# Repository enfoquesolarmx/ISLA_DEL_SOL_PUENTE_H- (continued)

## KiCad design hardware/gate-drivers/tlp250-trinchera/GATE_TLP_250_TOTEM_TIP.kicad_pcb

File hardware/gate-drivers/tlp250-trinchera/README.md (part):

# Módulo gate driver de medio puente H con TLP250H — modo trinchera (legacy) con tótem TIP41C/TIP42C

**Proyecto:** Puente H — prototipo SPWM "Isla del Sol" (inversor 48 V → 127 V / 60 Hz, 1000 W; modo cargador 1 kVA)
**Módulo:** gate driver de **medio puente H** (una rama: MOSFET alto + MOSFET bajo), de servicio / legacy, intercambiable con IRS2186 y UCC21520DW (misma interfaz, mismo firmware)
**Versión de placa:** V.0.1.NOV.26.J.G
**Estado:** diseño terminado (esquemático y layout); esquemático por bloques con guía de trinchera (2026-11-12). Pendiente: DRC final, fabricación y validación en banco
**Fecha:** 2026-11-02 · **Revisión:** 2026-11-03 (diseño final) · 2026-11-12 (esquemático por bloques)
**Documentos relacionados:** `identificacion_dt_pin9.md` (P9, llave en posición 8, poka-yoke), `compensacion_adaptativa_tiempo_muerto.md`

| Cara de componentes | Cara de soldadura |
| --- | --- |
|  |  |

*Izquierda: arriba, la bornera J1 de entrada, con R3/R4 (330 Ω) en serie con los LED y R1/R2 (10 kΩ) a GND; en medio, los **dos TLP250H** (DIP-8), uno por canal; abajo, los dos tótems **acostados**, TIP41C (NPN) y TIP42C (PNP) con sus resistencias de 2.2 Ω, la red de bootstrap (2.2 Ω 1 W + diodo rápido), los 2 × 10 µF del bootstrap y el header J5. Derecha: las leyendas **"TRENZAR H Y L CON GND"**, **"OPERACIÓN DT TLP250 = 1 µs"** y **"OJO: USAR SILICÓN RTV NEUTRO ENTRE TIPs"**, los 0.1 µF pegados a cada TLP, el 10 µF de 15 V, el zener Z1 de 18 V (1SMA5931B) y la **X** de la llave en la posición 8 de J5.*

*Esquemático por bloques (KiCad 9, hoja A3), pensado para quien arma y repara: **A** entrada J1 · **B** optoacoplador del canal alto (U1) · **C** optoacoplador del canal bajo (U2) · **D** 15 V del canal bajo · **E** bootstrap · **F** tótem alto · **G** tótem bajo · **H** salida J5 · **I** guía rápida de trinchera. Cada bloque dice qué medir y qué pasa si una pieza va al revés.*

## 0. Guía rápida de trinchera

**TLP250 o TLP250H: no son iguales.**

| | TLP250H (diseño) | TLP250 "viejo" (sin H, rescatado) |
| --- | --- | --- |
| Corriente de alimentación | **3 mA máx.** | **11 mA máx.** (7 mA típ.) |
| UVLO | Sí, 7.5–9.5 V | **No especificado** |
| Rama A (24 kHz, el bootstrap se recarga cada 42 µs) | ✓ | ✓ |
| Rama B (60 Hz, 8.3 ms sin recargar) | ✓ VB1 ≈ 11.8 V | ✗ VB1 cae ~5–8 V → el MOSFET alto queda a medio encender y sin protección |

**Regla:** un TLP250 sin "H" solo va en el módulo de la **rama A** (o en las dos en modo cargador, a 24 kHz). En la rama B del inversor, TLP250H u otro módulo (IRS2186, IR2110, UCC21520).

**Antes de soldar:**

| Pieza | Cuidado | Si se hace mal |
| --- | --- | --- |
| U1, U2 | Zócalo DIP-8, muesca hacia el pin 1; revisar la letra **H** | Al revés no enciende; sin H, ver la tabla anterior |
| R3, R4 | **330 Ω** con MCU de 5 V | Con 1 kΩ el LED no enciende bien (~1.7 mA) |
| J5 | **Quitar el pin 8** del header (llave) | El módulo podría entrar al revés |
| Z1 | Banda (cátodo) hacia **VB1** | Pone en corto el bootstrap: el MOSFET alto nunca enciende |
| Q1–Q4 | NPN (TIP41C / D44H11G) en Q1 y Q4, PNP (TIP42C / D45H11G) en Q2 y Q3; acostados, aletas sin tocarse | Cruzados: la salida no sigue a la entrada; aletas juntas: corto VB1–GND_K |
| TIPs | Silicón RTV **neutro** | El acético corroe; el caliente se ablanda a 60–80 °C |

**Prueba sin MOSFET** (15 V en J5-7; J5-4 a la tierra de la fuente; **J5-2 (VS1) unido a J5-4** para que cargue el bootstrap; J1 a la tarjeta de control o a 5 V):

| Medir | Entre | Debe dar |
| --- | --- | --- |
| Salidas con J1 suelto | HA_OUT (J5-1) y LA_OUT (J5-5) | 0 V |
| L = 5 V | LA_OUT a GND_K | ≈ 14 V |
| H = 5 V (después de un pulso de L) | HA_OUT a VS1 | ≈ 13 V |
| Corriente del LED | Caída en R3 o R4 | ≈ 3.3 V (~10 mA) |
| Aislamiento | J1-GND contra GND_K y contra VS1 | **Sin continuidad** |
| Tiempo muerto | Lo que reporta el MCU | **1 µs** (P9 abierto) |

---

## 1. Propósito

### 1.1 Qué maneja este módulo

Cada módulo es un **gate driver de medio puente**: maneja **una rama** del puente H, es decir, el **MOSFET del lado alto** (canal H, referido a VS1, alimentado por bootstrap) y el **MOSFET del lado bajo** (canal L, referido a GND_K) de esa rama.

```
            +48 V
              │
     HA ──► [MOSFET alto]          [MOSFET alto] ◄── HB
              │                         │
              ├── VS1 ──► transformador ◄── VS2 ──┤
              │                         │
     LA ──► [MOSFET bajo]          [MOSFET bajo] ◄── LB
              │                         │
             GND ───────────────────── GND
         └── módulo rama A ──┘    └── módulo rama B ──┘
```

- **El puente H completo usa dos módulos:** uno en la **rama A** (VS1) y otro en la **rama B** (VS2). Son el mismo módulo; en la rama B, las señales "H" y "L" de J1 manejan HB y LB, y el pin "VS1" de J5 se conecta a VS2.
- **Inversor (modulación híbrida):** el módulo de la rama A conmuta a **24 kHz** y el de la rama B a **60 Hz**.
- **Cargador (unipolar):** los dos módulos conmutan a **24 kHz**.
- Cada posición (alto o bajo) puede tener **1 o 2 MOSFET en paralelo** (sección 5).
- Se pueden mezclar tecnologías entre ramas (por ejemplo, UCC21520 en la rama A y TLP250 en la rama B): el MCU lee P9 de cada módulo y, si cualquiera pide 1 µs, usa 1 µs en todo el puente.

### 1.2 Por qué existe

Este módulo existe para **cuando TI o Infineon no llegan**. Es una opción **educativa y de supervivencia**: demuestra que el puente H puede operar con componentes legacy que se consiguen en cualquier tienda de electrónica o se rescatan de equipos viejos (variadores, UPS, soldadoras inverter, fuentes, amplificadores).

| Criterio | Módulos IRS2186 / UCC21520 | Módulo TLP250 (este) |
| --- | --- | --- |
| Costo y número de componentes | **Menor** ✓ | Mayor |
| Desempeño (DT, THD) | **500 ns, THD ~0.8 %** ✓ | 1 µs, THD ~1.6 % |
| Disponibilidad en zonas aisladas | Baja (distribuidor, importación) | **Alta: tienda local o rescate** ✓ |
| Reparación a mano | SMD fino | **DIP y TO-220, cautín común** ✓ |
| Aislamiento entrada / potencia | IRS: no aislado · UCC: aislado | **Aislado (optoacoplador)** ✓ |
| Valor educativo | Driver integrado ("caja negra") | **Cada etapa visible y medible** ✓ |

**Conclusión de diseño:** para producción se usan IRS2186 o UCC21520. Este módulo no busca eficientar; busca que **siempre exista una alternativa**. La infraestructura que lo soporta (P9 y llave en posición 8) cuesta ~1 USD y queda en todas las tarjetas.

---

## 2. Interfaz

### 2.1 J1 — entrada, hacia la tarjeta de control (bornera de 5 terminales)

| Terminal | Señal | En este módulo |
| --- | --- | --- |
| 1 | H | Ánodo del LED de U1 (vía R3) |
| 2 | GND | Cátodo del LED de U1 (trenzar con H) |
| 3 | L | Ánodo del LED de U2 (vía R4) |
| 4 | GND | Cátodo del LED de U2 (trenzar con L) |
| **5** | **P9 — ID DT** | **Abierto, sin pista** → el MCU usa **1 µs** |

- Serigrafía: **"TRENZAR H Y L CON GND"** y **"OPERACION DT TLP250=1US"**.
- **P9 tiene como vecino un GND (terminal 4).** Cable con **puntas estañadas o terminal**, sin hilos sueltos. Opcional: no instalar el cable P9 (la pull-up de la tarjeta de control lee 1 → 1 µs).
- El GND de J1 es el GND del MCU y **no se une a GND_K ni a la potencia dentro del módulo**: el optoacoplador aísla la entrada.

### 2.2 J5 — salida, hacia la tarjeta del puente H (header de 9 posiciones, 2.54 mm)

| Pin | Señal | En este módulo |
| --- | --- | --- |
| 1 | HA_OUT | Emisores del tótem H |
| 2 | VS1 | Referencia del canal H |
| 3 | — | Libre (separación del nodo conmutado) |
| 4 | GND_K | Referencia Kelvin del canal L |
| 5 | LA_OUT | Emisores del tótem L |
| 6 | — | **Sin conectar** en este módulo (la entrada está aislada); marcado como no conectado en el esquemático |
| 7 | 15 V | Alimentación |
| 8 | — | **Llave mecánica:** sin pad; **quitar el pin 8 del header**; "X" en serigrafía |
| 9 | — | Reservado, abierto |

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
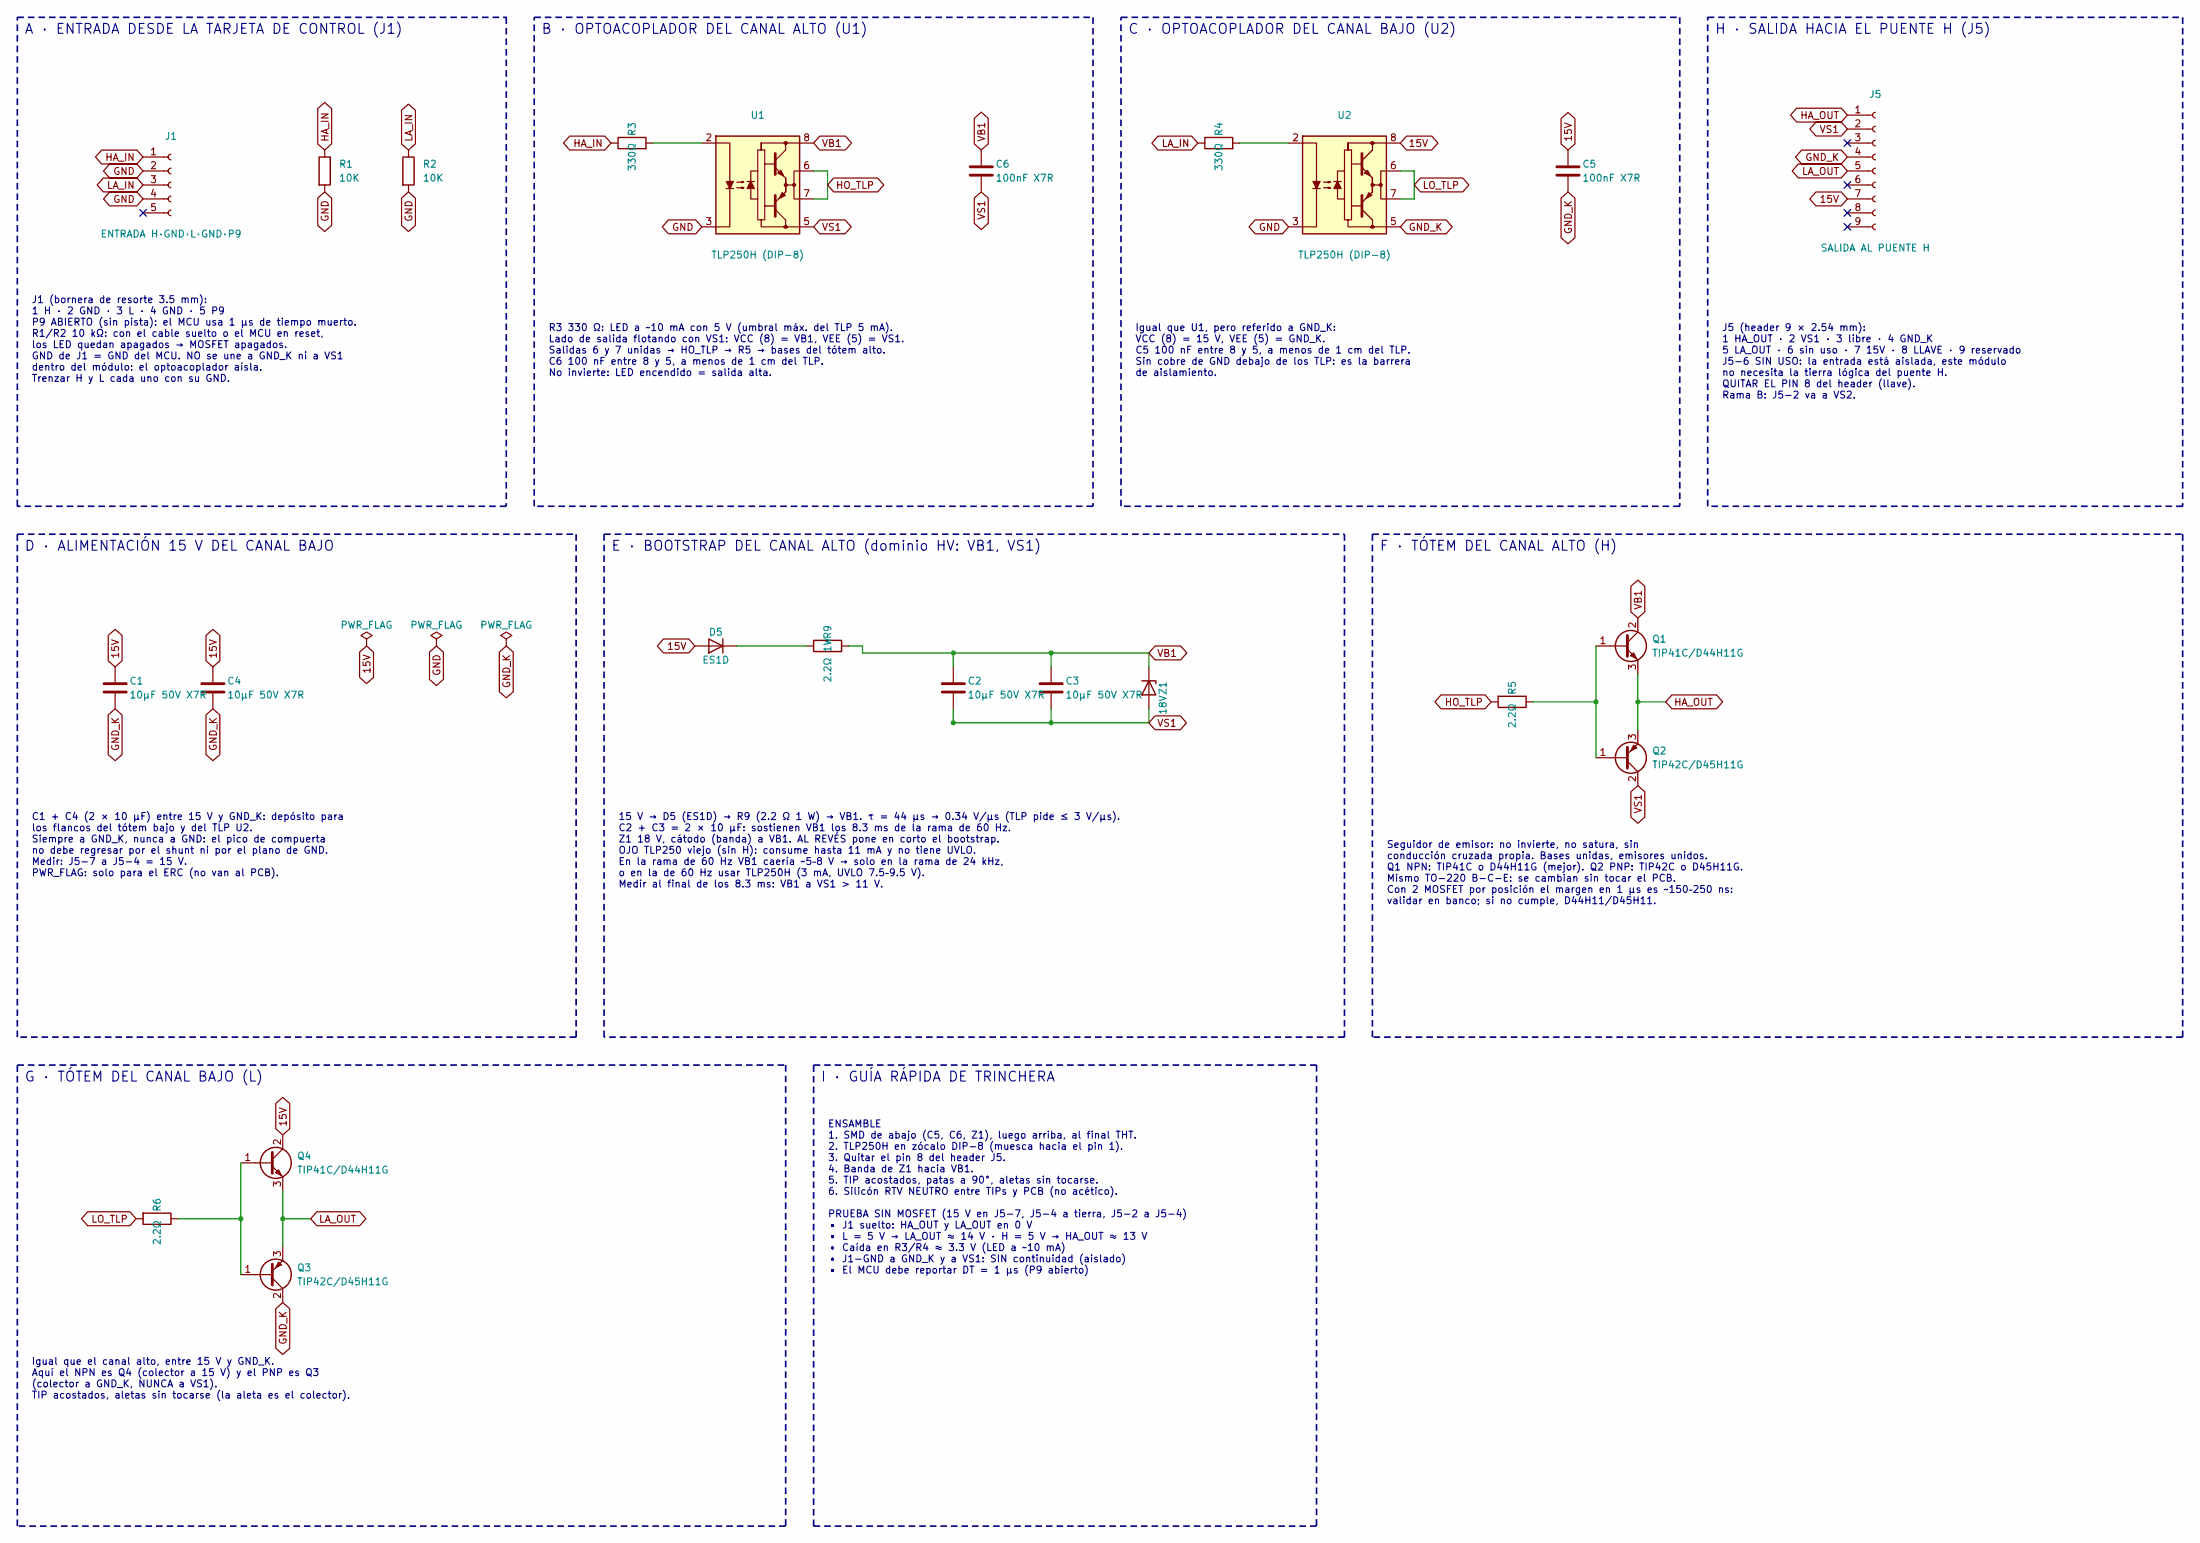
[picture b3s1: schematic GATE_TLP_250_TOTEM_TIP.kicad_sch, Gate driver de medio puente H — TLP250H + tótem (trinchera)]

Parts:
C1, C2, C3, C4: 10µF 50V X7R; C_1206_3216Metric
C5, C6: 100nF X7R; C_1206_3216Metric
D5: ES1D; D_SMA
J1: ENTRADA H·GND·L·GND·P9; PhoenixContact_SPT_1.5_5-H-3.5_1x05_P3.5mm_Horizontal
J5: SALIDA AL PUENTE H; PinHeader_1x09_P2.54mm_Vertical
Q1, Q4: TIP41C/D44H11G; TO-220-3_Vertical
Q2, Q3: TIP42C/D45H11G; TO-220-3_Vertical
R1, R2: 10K; R_1206_3216Metric_Pad1.30x1.75mm_HandSolder
R3, R4: 330Ω; R_1206_3216Metric_Pad1.30x1.75mm_HandSolder
R5, R6: 2.2Ω; R_1206_3216Metric_Pad1.30x1.75mm_HandSolder
R9: 2.2Ω 1W; R_1210_3225Metric
U1, U2: TLP250H (DIP-8); DIP-8_W7.62mm
Z1: 18V; D_SMA

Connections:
15V: C1.1, C4.1, C5.1, D5.2 (A), J5.7, Q4.2 (C), U2.8 (VCC)
GND: J1.2, J1.4, R1.2, R2.2, U1.3 (C), U2.3 (C)
GND_K: C1.2, C4.2, C5.2, J5.4, Q3.2 (C), U2.5 (VEE)
HA_IN: J1.1, R1.1, R3.1
HA_OUT: J5.1, Q1.3 (E), Q2.3 (E)
HO_TLP: R5.2, U1.6 (VO), U1.7 (VO)
LA_IN: J1.3, R2.1, R4.1
LA_OUT: J5.5, Q3.3 (E), Q4.3 (E)
LO_TLP: R6.2, U2.6 (VO), U2.7 (VO)
unnamed: D5.1 (K), R9.2
unnamed: Q1.1 (B), Q2.1 (B), R5.1
unnamed: Q3.1 (B), Q4.1 (B), R6.1
unnamed: R3.2, U1.2 (A)
unnamed: R4.2, U2.2 (A)
VB1: C2.1, C3.1, C6.1, Q1.2 (C), R9.1, U1.8 (VCC), Z1.1 (K)
VS1: C2.2, C3.2, C6.2, J5.2, Q2.2 (C), U1.5 (VEE), Z1.2 (A)

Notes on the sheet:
A · ENTRADA DESDE LA TARJETA DE CONTROL (J1)
J1 (bornera de resorte 3.5 mm): 1 H · 2 GND · 3 L · 4 GND · 5 P9 P9 ABIERTO (sin pista): el MCU usa 1 µs de tiempo muerto. R1/R2 10 kΩ: con el cable suelto o el MCU en reset, los LED quedan apagados → MOSFET apagados. GND de J1 = GND del MCU. NO se une a GND_K ni a VS1 dentro del módulo: el optoaco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
B · OPTOACOPLADOR DEL CANAL ALTO (U1)
R3 330 Ω: LED a ~10 mA con 5 V (umbral máx. del TLP 5 mA). Lado de salida flotando con VS1: VCC (8) = VB1, VEE (5) = VS1. Salidas 6 y 7 unidas → HO_TLP → R5 → bases del tótem alto. C6 100 nF entre 8 y 5, a menos de 1 cm del TLP. No invierte: LED encendido = salida alta.
C · OPTOACOPLADOR DEL CANAL BAJO (U2)
Igual que U1, pero referido a GND_K: VCC (8) = 15 V, VEE (5) = GND_K. C5 100 nF entre 8 y 5, a menos de 1 cm del TLP. Sin cobre de GND debajo de los TLP: es la barrera de aislamiento.
H · SALIDA HACIA EL PUENTE H (J5)
J5 (header 9 × 2.54 mm): 1 HA_OUT · 2 VS1 · 3 libre · 4 GND_K 5 LA_OUT · 6 sin uso · 7 15V · 8 LLAVE · 9 reservado J5-6 SIN USO: la entrada está aislada, este módulo no necesita la tierra lógica del puente H. QUITAR EL PIN 8 del header (llave). Rama B: J5-2 va a VS2.
D · ALIMENTACIÓN 15 V DEL CANAL BAJO
C1 + C4 (2 × 10 µF) entre 15 V y GND_K: depósito para los flancos del tótem bajo y del TLP U2. Siempre a GND_K, nunca a GND: el pico de compuerta no debe regresar por el shunt ni por el plano de GND. Medir: J5-7 a J5-4 = 15 V. PWR_FLAG: solo para el ERC (no van al PCB).
E · BOOTSTRAP DEL CANAL ALTO (dominio HV: VB1, VS1)
15 V → D5 (ES1D) → R9 (2.2 Ω 1 W) → VB1. τ = 44 µs → 0.34 V/µs (TLP pide ≤ 3 V/µs). C2 + C3 = 2 × 10 µF: sostienen VB1 los 8.3 ms de la rama de 60 Hz. Z1 18 V, cátodo (banda) a VB1. AL REVÉS pone en corto el bootstrap. OJO TLP250 viejo (sin H): consume hasta 11 mA y no tiene UVLO. En la rama de 60 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
F · TÓTEM DEL CANAL ALTO (H)
Seguidor de emisor: no invierte, no satura, sin conducción cruzada propia. Bases unidas, emisores unidos. Q1 NPN: TIP41C o D44H11G (mejor). Q2 PNP: TIP42C o D45H11G. Mismo TO-220 B-C-E: se cambian sin tocar el PCB. Con 2 MOSFET por posición el margen en 1 µs es ~150–250 ns: validar en banco; si no 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
G · TÓTEM DEL CANAL BAJO (L)
Igual que el canal alto, entre 15 V y GND_K. Aquí el NPN es Q4 (colector a 15 V) y el PNP es Q3 (colector a GND_K, NUNCA a VS1). TIP acostados, aletas sin tocarse (la aleta es el colector).
I · GUÍA RÁPIDA DE TRINCHERA
ENSAMBLE 1. SMD de abajo (C5, C6, Z1), luego arriba, al final THT. 2. TLP250H en zócalo DIP-8 (muesca hacia el pin 1). 3. Quitar el pin 8 del header J5. 4. Banda de Z1 hacia VB1. 5. TIP acostados, patas a 90°, aletas sin tocarse. 6. Silicón RTV NEUTRO entre TIPs y PCB (no acético). PRUEBA SIN MOSFE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

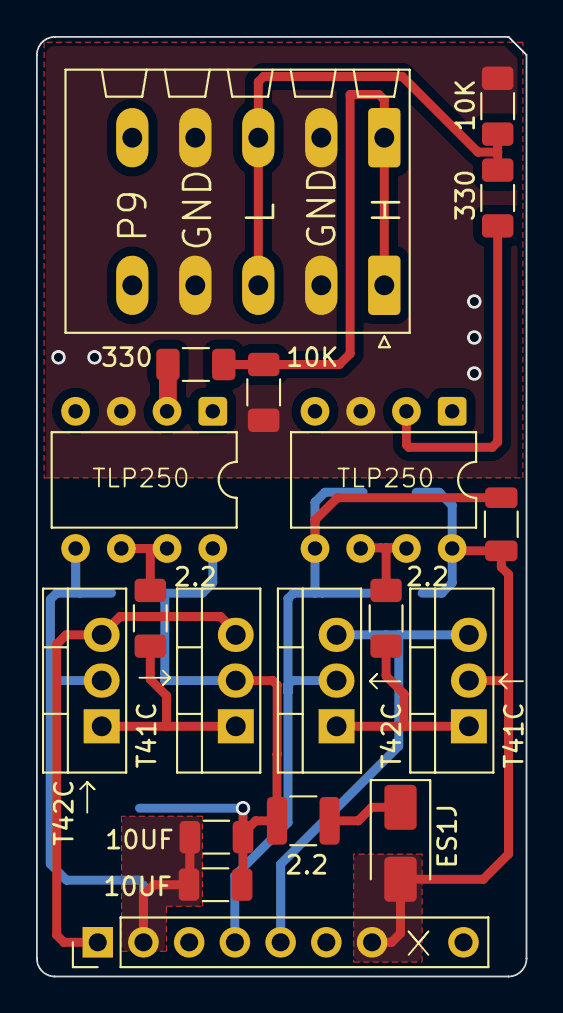
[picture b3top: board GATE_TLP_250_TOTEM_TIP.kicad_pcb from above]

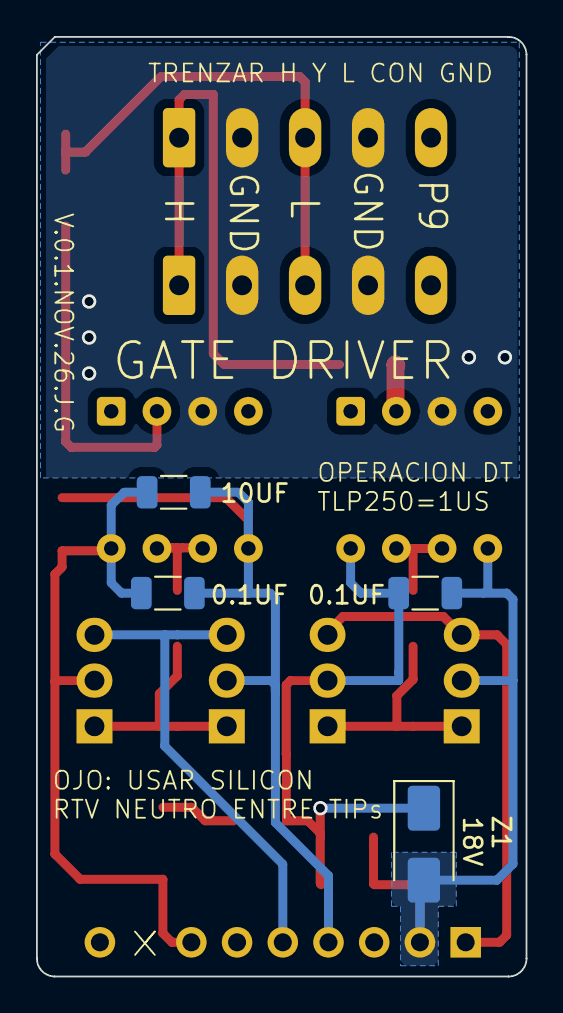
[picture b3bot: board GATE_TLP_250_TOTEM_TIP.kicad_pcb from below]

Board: 2 copper layers, 27.2 x 52.2 mm, 23 parts (4 on the bottom side), 16 nets.

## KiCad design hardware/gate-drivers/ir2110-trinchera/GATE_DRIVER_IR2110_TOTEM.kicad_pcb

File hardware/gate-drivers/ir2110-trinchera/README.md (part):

# Módulo gate driver de medio puente H con IR2110 + tótem TIP41C/TIP42C — modo trinchera

**Proyecto:** Puente H — prototipo SPWM "Isla del Sol" (inversor 48 V → 127 V / 60 Hz, 1000 W; modo cargador 1 kVA)
**Módulo:** gate driver de **medio puente H** (una rama: MOSFET alto + MOSFET bajo), legacy / trinchera, con tótem por canal
**Intercambiable con:** IRS2186, UCC21520DW y TLP250 de trinchera (misma interfaz J2/J5, mismo firmware)
**Versión de placa:** V.0.1.NOV.26.J.G
**Estado:** diseño terminado; DRC con 0 errores y 0 elementos sin conectar; esquemático por bloques con guía de trinchera (2026-11-12). Pendiente: fabricación y validación en banco
**Fecha:** 2026-11-04 (esquemático por bloques: 2026-11-12)
**Documentos relacionados:** [`docs/identificacion_dt_pin9.md`](../../../docs/identificacion_dt_pin9.md), [`docs/sensado_corriente.md`](../../../docs/sensado_corriente.md), [módulo TLP250](../tlp250-trinchera/README.md), [módulo IRS2186](../irs2186/README.md)

| Cara de componentes | Cara de soldadura |
| --- | --- |
|  |  |

*Izquierda: arriba, la bornera J2 de entrada con R1 y R2 (10 kΩ, pull-down de HIN y LIN); en medio, el **IR2110 en DIP-14** con sus capacitores X7R; abajo, los **cuatro TO-220 del tótem** (TIP41C o D44H11 como NPN, TIP42C o D45H11 como PNP) y el header J5 hacia el puente H (H · VS1 · · · GK · L · G · 15V · llave · NC). La leyenda **"USAR SILICÓN RTV NEUTRO ENTRE TIPs"** recuerda fijar los transistores a la tarjeta con silicón de curado neutro. Derecha: la leyenda **"ATENCIÓN: DT = 1 µs — VALIDAR MOSFET Y SW"**, el regulador **78L05** (SOT-89) que da los 5 V de VDD, la red de bootstrap (2.2 Ω 1 W + ES1D), los dos **zener de 18 V** (Z1: VB1–VS1 y Z2: 15V–GND_K) y la **X** de la llave en la posición 8 de J5.*

*Esquemático por bloques (KiCad 9, hoja A3), pensado para quien arma y repara: **A** entrada J2 · **B** lógica de 5 V con 78L05 · **C** IR2110 · **D** 15 V del lado bajo · **E** bootstrap · **F** tótem alto · **G** tótem bajo · **H** salida J5 · **I** guía rápida de trinchera (ensamble y prueba sin MOSFET). Cada bloque dice qué medir y qué pasa si una pieza va al revés.*

## 0. Guía rápida de trinchera

**Antes de soldar:**

| Pieza | Cuidado | Si se hace mal |
| --- | --- | --- |
| U1 IR2110 | En **zócalo DIP-14**, muesca hacia el pin 1 | Se cambia sin cautín; al revés se quema al conectar |
| J5 | **Quitar el pin 8** del header (llave) | El módulo podría entrar al revés en el puente H |
| Z1 | Banda (cátodo) hacia **VB1** | Pone en corto el bootstrap: el MOSFET alto nunca enciende |
| Z2 | Banda (cátodo) hacia **15 V** | Se calienta y jala los 15 V |
| Q1–Q4 | NPN (TIP41C / D44H11G) arriba, PNP (TIP42C / D45H11G) abajo; acostados, aletas sin tocarse | NPN y PNP cruzados: la salida no sigue a la entrada |
| TIPs | Silicón RTV **neutro** entre los cuerpos y el PCB | El silicón acético corroe las patas |

**Prueba sin MOSFET** (15 V en J5-7; J5-6 y J5-4 a la tierra de la fuente; **J5-2 (VS1) unido a J5-4** para que cargue el bootstrap; J2 a la tarjeta de control o a 5 V):

| Medir | Entre | Debe dar |
| --- | --- | --- |
| VDD | Pin 9 y pin 13 del IR2110 | 5.0 V ± 0.25 V |
| VCC | Pin 3 y pin 2 | 15 V |
| SD | Pin 11 a GND | 0 V |
| Salidas con J2 suelto | HA_OUT (J5-1) y LA_OUT (J5-5) | 0 V |
| L = 5 V | LA_OUT a GND_K | ≈ 14 V (15 V menos el V_BE del tótem) |
| H = 5 V (después de un pulso de L, para cargar el bootstrap) | HA_OUT a VS1 | ≈ 13 V |
| Tiempo muerto | Lo que reporta el MCU | **1 µs** (P9 abierto) |

> Valores verificados contra `GATE_DRIVER_IR2110_TOTEM.kicad_pcb` (2026-11-04). Lo marcado *(verificar)* depende de la hoja de datos.

---
## 1. Qué maneja este módulo

Cada módulo maneja **una rama** del puente H: el **MOSFET del lado alto** (HO, referido a VS, alimentado por bootstrap) y el **MOSFET del lado bajo** (LO, referido a COM / GND_K).

```
            +48 V
              │
     HA ──► [MOSFET alto]          [MOSFET alto] ◄── HB
              │                         │
              ├── VS1 ──► transformador ◄── VS2 ──┤
              │                         │
     LA ──► [MOSFET bajo]          [MOSFET bajo] ◄── LB
              │                         │
             GND ───────────────────── GND
         └── módulo rama A ──┘    └── módulo rama B ──┘
```

- **El puente completo usa dos módulos iguales:** rama A (VS1) y rama B (VS2). En la rama B, "H" y "L" de J2 manejan HB y LB, y el pin "VS1" de J5 va a VS2.
- **Inversor (modulación híbrida):** rama A a **24 kHz**, rama B a **60 Hz**. **Cargador (unipolar):** las dos ramas a **24 kHz**.
- **Alcance: de 1 a 5 MOSFET por posición** (sección 6).

### 1.1 Por qué existe: modo trinchera

Igual que el módulo TLP250, este módulo existe para **cuando los drivers modernos no llegan**. El IR2110 (International Rectifier, hoy Infineon) es el driver de medio puente **más fácil de conseguir o rescatar**: está en variadores, soldadoras inverter y UPS viejos, y en casi cualquier tienda de electrónica. Viene en **DIP-14**: se monta en zócalo y se cambia sin cautín. Todo el módulo se arma con partes de tienda local.

| | TLP250 + tótem | **IR2110 + tótem (este)** |
| --- | --- | --- |
| Driver | Optoacoplador DIP-8, uno por canal | DIP-14, un chip para los dos canales |
| Aislamiento de la entrada | Sí (óptico) | Parcial: **VSS y COM separados**, hasta ±5 V |
| Diferencia de retardo entre canales | Hasta **400 ns** | **10–20 ns** |
| Margen dentro de 1 µs | ~150–250 ns con 2 IRF100P219 | **Mucho mayor** |
| Corriente propia | ~2 A | 2 A |
| MOSFET por posición | 1–2 IRF100P219 | **1–5** (por ejemplo 5 × IRF540N) |

---

## 2. Interfaz

### 2.1 J2 — entrada, hacia la tarjeta de control ("J1" de la interfaz)

Conector **Phoenix Contact SPT 1,5/5-H-3,5** (5 posiciones, paso 3.5 mm, de resorte), igual que el módulo IRS2186.

| Terminal | Señal | En este módulo |
| --- | --- | --- |
| 1 | H | HIN del IR2110 (pin 10), 10 kΩ a GND |
| 2 | GND | Tierra lógica = VSS (trenzar con H) |
| 3 | L | LIN del IR2110 (pin 12), 10 kΩ a GND |
| 4 | GND | Tierra lógica = VSS (trenzar con L) |
| **5** | **P9 — ID DT** | **Abierto, sin pista** → el MCU usa **1 µs** |

### 2.2 J5 — salida, hacia la tarjeta del puente H (header de 9 posiciones, 2.54 mm)

| Pin | Señal | Nota |
| --- | --- | --- |
| 1 | H (HA_OUT) | Emisores del tótem H |
| 2 | VS1 | Referencia del canal H |
| 3 | — | Libre (separación del nodo conmutado) |
| 4 | GK (GND_K) | Referencia Kelvin del canal L = **COM** |
| 5 | L (LA_OUT) | Emisores del tótem L |
| 6 | G (GND) | **Tierra lógica (VSS)**: retorno del 78L05 hacia la tarjeta del puente H |
| 7 | 15 V | Alimentación |
| 8 | **X** | **Llave mecánica:** sin pad; **quitar el pin 8 del header** |
| 9 | NC | Reservado |

### 2.3 Tierras: VSS y COM separados

El IR2110 tiene **dos tierras**: **VSS** (lógica) y **COM** (retorno del lado bajo), con hasta **±5 V** de diferencia permitida.

| Zona | Referencia | Componentes |
| --- | --- | --- |
| Lógica | **GND (VSS)** | J2, R1, R2, VSS (13), SD (11), 78L05, capacitor de entrada y de salida del 78L05, **J5-6** |
| Canal L (potencia) | **GND_K (COM)** | COM (2), colector de Q4 (PNP), C2, C4, C6, C8, Z2 |
| Canal H (HV, flota con VS1) | **VS1** | VS (5), Q2 colector, C3, C5, C9, Z1 |

- **J5-6 a GND lógico** (a diferencia del TLP250, que deja J5-6 sin conectar): el 78L05 toma sus 15 V de J5-7, así que su corriente regresa por el camino corto J5-6. Además, VSS queda bien referido respecto a COM.
- **COM va a GND_K (J5-4):** la corriente de compuerta del canal bajo regresa por GND_K y **no pasa por la tierra lógica**. Es la ventaja del IR2110 sobre el IRS2186.
- GND y GND_K se unen en **un solo punto en la tarjeta del puente H**, nunca dentro del módulo.
- **Lazo de tierra:** igual que con el IRS2186, el GND del cable J2 es un camino más hacia la tarjeta de control. Se controla con **par trenzado H/GND y L/GND** y la unión única de tierras.
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
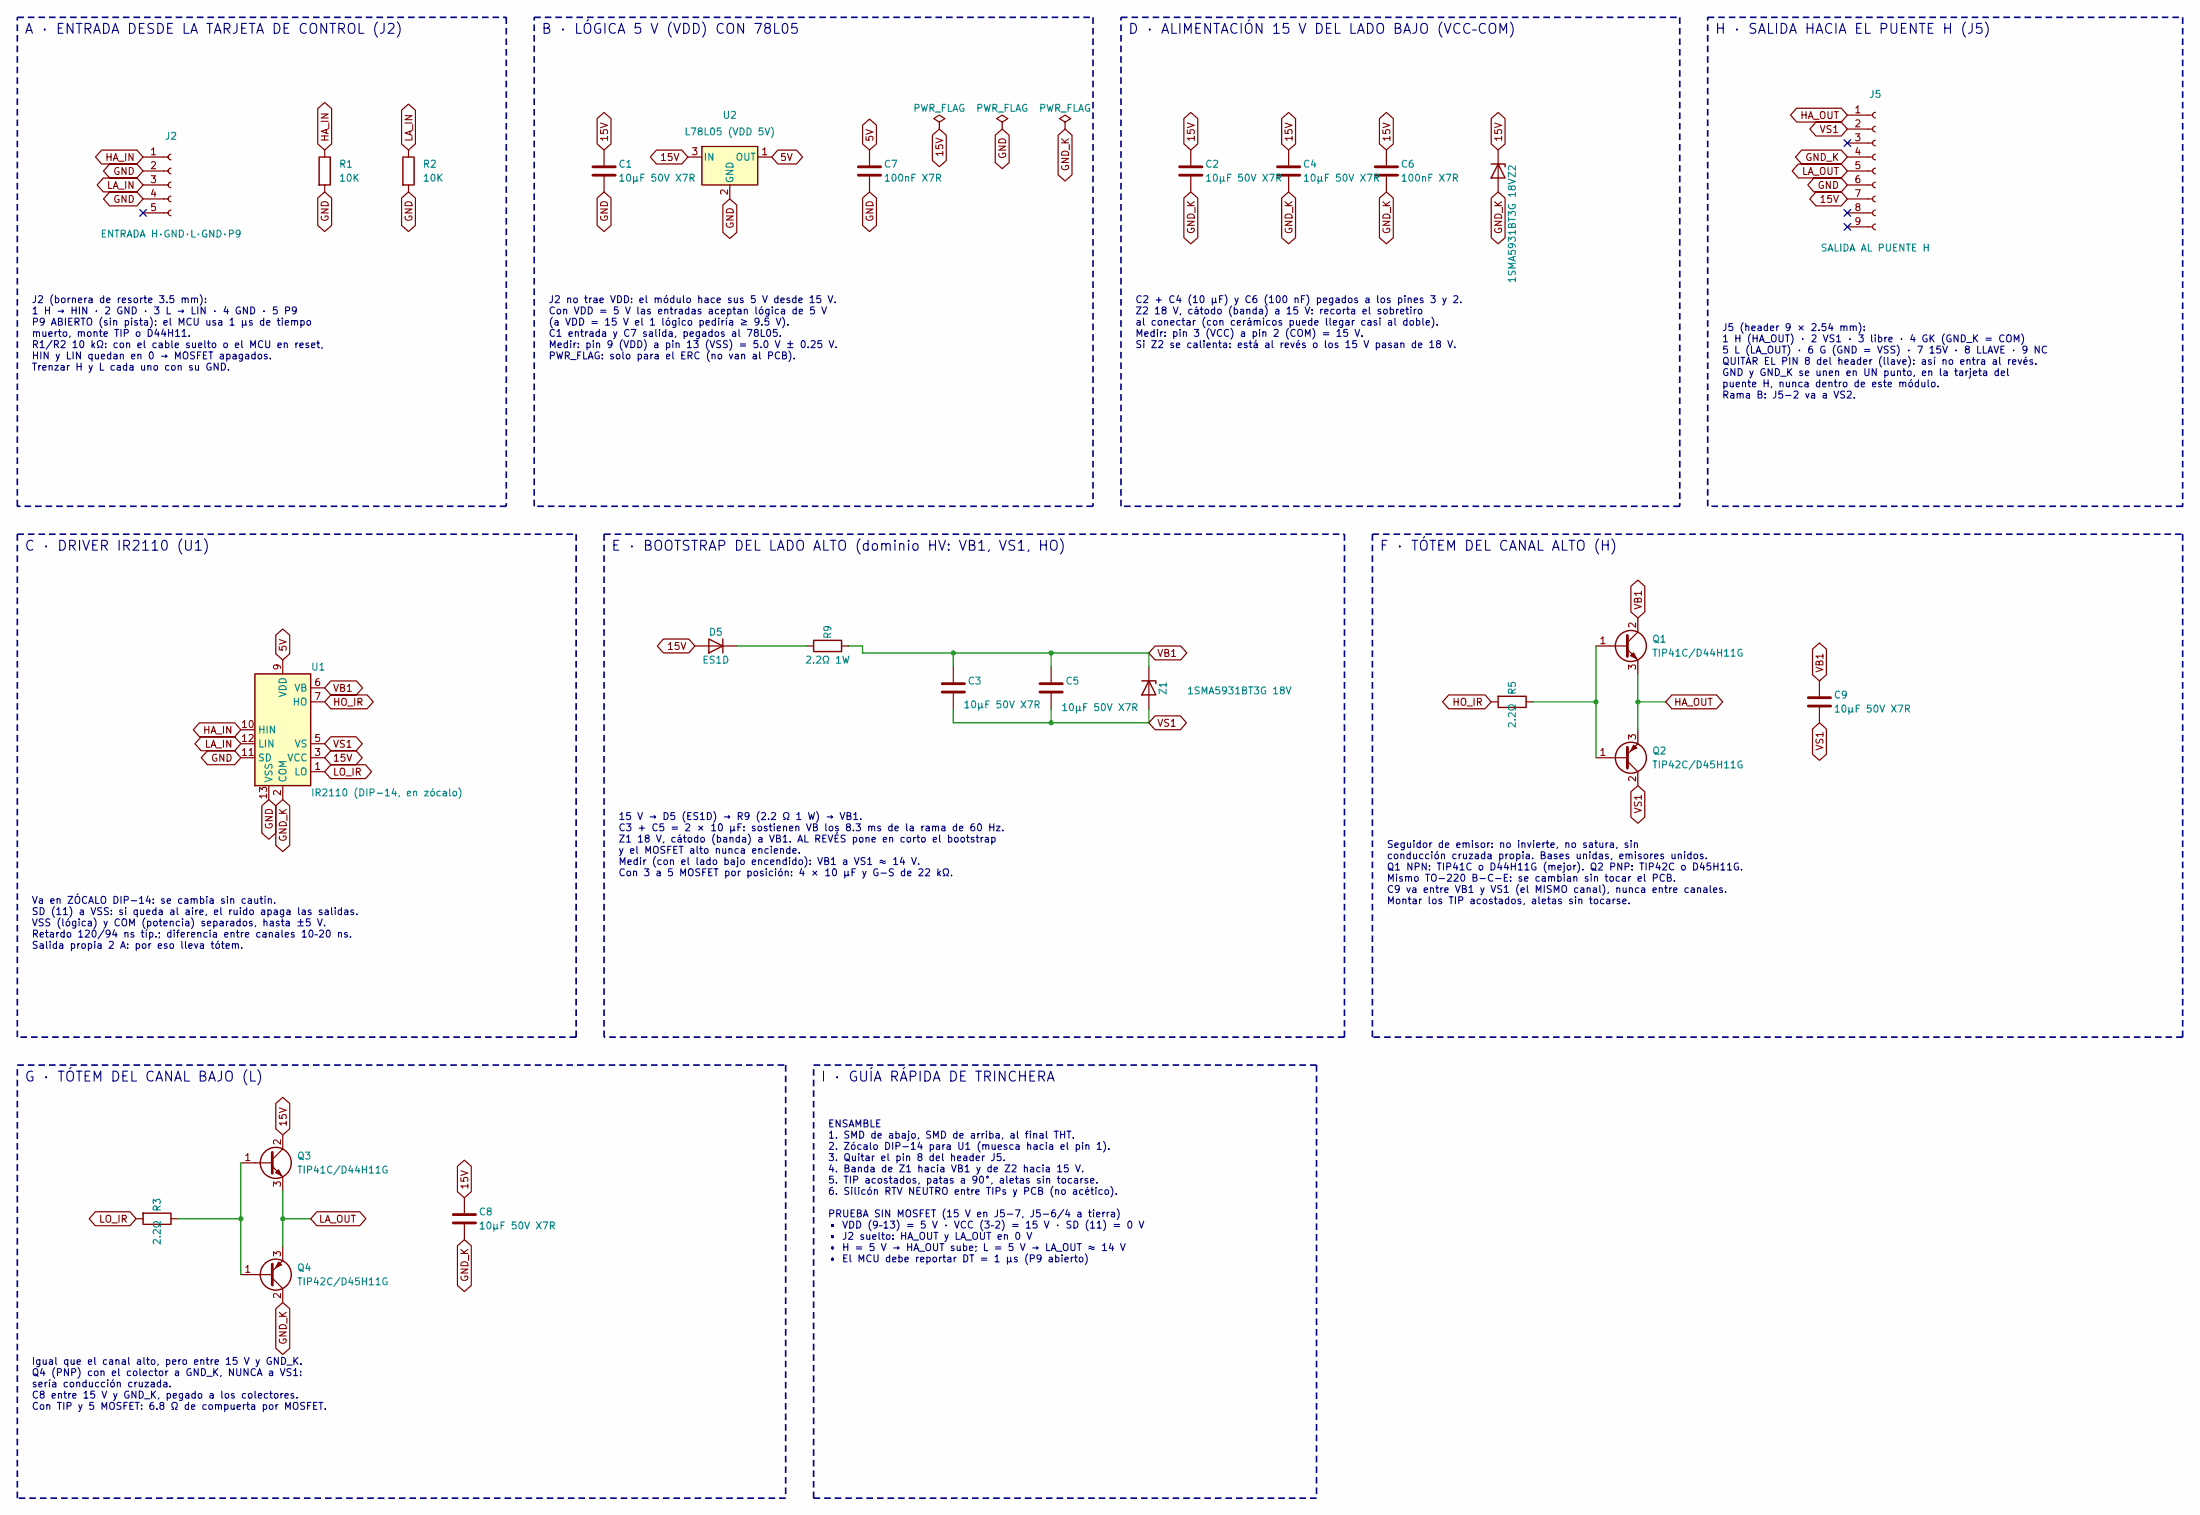
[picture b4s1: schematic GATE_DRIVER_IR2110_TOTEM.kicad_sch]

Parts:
C1, C2, C3, C4, C5, C8, C9: 10µF 50V X7R; C_1210_3225Metric_Pad1.33x2.70mm_HandSolder
C6, C7: 100nF X7R; C_1206_3216Metric
D5: ES1D; D_SMA
J2: ENTRADA H·GND·L·GND·P9; PhoenixContact_SPT_1.5_5-H-3.5_1x05_P3.5mm_Horizontal
J5: SALIDA AL PUENTE H; PinHeader_1x09_P2.54mm_Vertical
Q1, Q3: TIP41C/D44H11G; TO-220-3_Vertical
Q2, Q4: TIP42C/D45H11G; TO-220-3_Vertical
R1, R2: 10K; R_1206_3216Metric_Pad1.30x1.75mm_HandSolder
R3, R5: 2.2Ω; R_1206_3216Metric_Pad1.30x1.75mm_HandSolder
R9: 2.2Ω 1W; R_1210_3225Metric
U1: IR2110 (DIP-14, en zócalo); DIP-14_W7.62mm
U2: L78L05 (VDD 5V); SOT-89-3
Z1, Z2: 1SMA5931BT3G 18V; D_SMA

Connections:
5V: C7.1, U1.9 (VDD), U2.1 (OUT)
15V: C1.1, C2.1, C4.1, C6.1, C8.1, D5.2 (A), J5.7, Q3.2 (C), U1.3 (VCC), U2.3 (IN), Z2.1 (K)
GND: C1.2, C7.2, J2.2, J2.4, J5.6, R1.2, R2.2, U1.11 (SD), U1.13 (VSS), U2.2 (GND)
GND_K: C2.2, C4.2, C6.2, C8.2, J5.4, Q4.2 (C), U1.2 (COM), Z2.2 (A)
HA_IN: J2.1, R1.1, U1.10 (HIN)
HA_OUT: J5.1, Q1.3 (E), Q2.3 (E)
HO_IR: R5.2, U1.7 (HO)
LA_IN: J2.3, R2.1, U1.12 (LIN)
LA_OUT: J5.5, Q3.3 (E), Q4.3 (E)
LO_IR: R3.2, U1.1 (LO)
unnamed: D5.1 (K), R9.2
unnamed: Q1.1 (B), Q2.1 (B), R5.1
unnamed: Q3.1 (B), Q4.1 (B), R3.1
VB1: C3.1, C5.1, C9.1, Q1.2 (C), R9.1, U1.6 (VB), Z1.1 (K)
VS1: C3.2, C5.2, C9.2, J5.2, Q2.2 (C), U1.5 (VS), Z1.2 (A)

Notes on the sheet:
H · SALIDA HACIA EL PUENTE H (J5)
ENSAMBLE 1. SMD de abajo, SMD de arriba, al final THT. 2. Zócalo DIP-14 para U1 (muesca hacia el pin 1). 3. Quitar el pin 8 del header J5. 4. Banda de Z1 hacia VB1 y de Z2 hacia 15 V. 5. TIP acostados, patas a 90°, aletas sin tocarse. 6. Silicón RTV NEUTRO entre TIPs y PCB (no acético). PRUEBA SIN 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
I · GUÍA RÁPIDA DE TRINCHERA
C2 + C4 (10 µF) y C6 (100 nF) pegados a los pines 3 y 2. Z2 18 V, cátodo (banda) a 15 V: recorta el sobretiro al conectar (con cerámicos puede llegar casi al doble). Medir: pin 3 (VCC) a pin 2 (COM) = 15 V. Si Z2 se calienta: está al revés o los 15 V pasan de 18 V.
E · BOOTSTRAP DEL LADO ALTO (dominio HV: VB1, VS1, HO)
A · ENTRADA DESDE LA TARJETA DE CONTROL (J2)
F · TÓTEM DEL CANAL ALTO (H)
Seguidor de emisor: no invierte, no satura, sin conducción cruzada propia. Bases unidas, emisores unidos. Q1 NPN: TIP41C o D44H11G (mejor). Q2 PNP: TIP42C o D45H11G. Mismo TO-220 B-C-E: se cambian sin tocar el PCB. C9 va entre VB1 y VS1 (el MISMO canal), nunca entre canales. Montar los TIP acostado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
B · LÓGICA 5 V (VDD) CON 78L05
Igual que el canal alto, pero entre 15 V y GND_K. Q4 (PNP) con el colector a GND_K, NUNCA a VS1: sería conducción cruzada. C8 entre 15 V y GND_K, pegado a los colectores. Con TIP y 5 MOSFET: 6.8 Ω de compuerta por MOSFET.
D · ALIMENTACIÓN 15 V DEL LADO BAJO (VCC–COM)
Va en ZÓCALO DIP-14: se cambia sin cautín. SD (11) a VSS: si queda al aire, el ruido apaga las salidas. VSS (lógica) y COM (potencia) separados, hasta ±5 V. Retardo 120/94 ns típ.; diferencia entre canales 10–20 ns. Salida propia 2 A: por eso lleva tótem.
G · TÓTEM DEL CANAL BAJO (L)
C · DRIVER IR2110 (U1)
15 V → D5 (ES1D) → R9 (2.2 Ω 1 W) → VB1. C3 + C5 = 2 × 10 µF: sostienen VB los 8.3 ms de la rama de 60 Hz. Z1 18 V, cátodo (banda) a VB1. AL REVÉS pone en corto el bootstrap y el MOSFET alto nunca enciende. Medir (con el lado bajo encendido): VB1 a VS1 ≈ 14 V. Con 3 a 5 MOSFET por posición: 4 × 10 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
J5 (header 9 × 2.54 mm): 1 H (HA_OUT) · 2 VS1 · 3 libre · 4 GK (GND_K = COM) 5 L (LA_OUT) · 6 G (GND = VSS) · 7 15V · 8 LLAVE · 9 NC QUITAR EL PIN 8 del header (llave): así no entra al revés. GND y GND_K se unen en UN punto, en la tarjeta del puente H, nunca dentro de este módulo. Rama B: J5-2 va a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
J2 (bornera de resorte 3.5 mm): 1 H → HIN · 2 GND · 3 L → LIN · 4 GND · 5 P9 P9 ABIERTO (sin pista): el MCU usa 1 µs de tiempo muerto, monte TIP o D44H11. R1/R2 10 kΩ: con el cable suelto o el MCU en reset, HIN y LIN quedan en 0 → MOSFET apagados. Trenzar H y L cada uno con su GND.
J2 no trae VDD: el módulo hace sus 5 V desde 15 V. Con VDD = 5 V las entradas aceptan lógica de 5 V (a VDD = 15 V el 1 lógico pediría ≥ 9.5 V). C1 entrada y C7 salida, pegados al 78L05. Medir: pin 9 (VDD) a pin 13 (VSS) = 5.0 V ± 0.25 V. PWR_FLAG: solo para el ERC (no van al PCB).

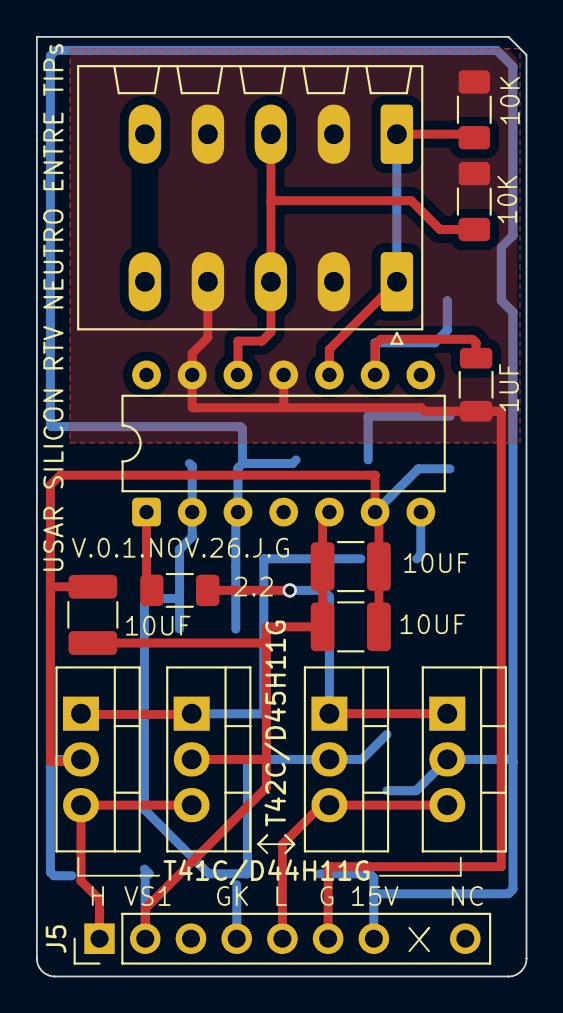
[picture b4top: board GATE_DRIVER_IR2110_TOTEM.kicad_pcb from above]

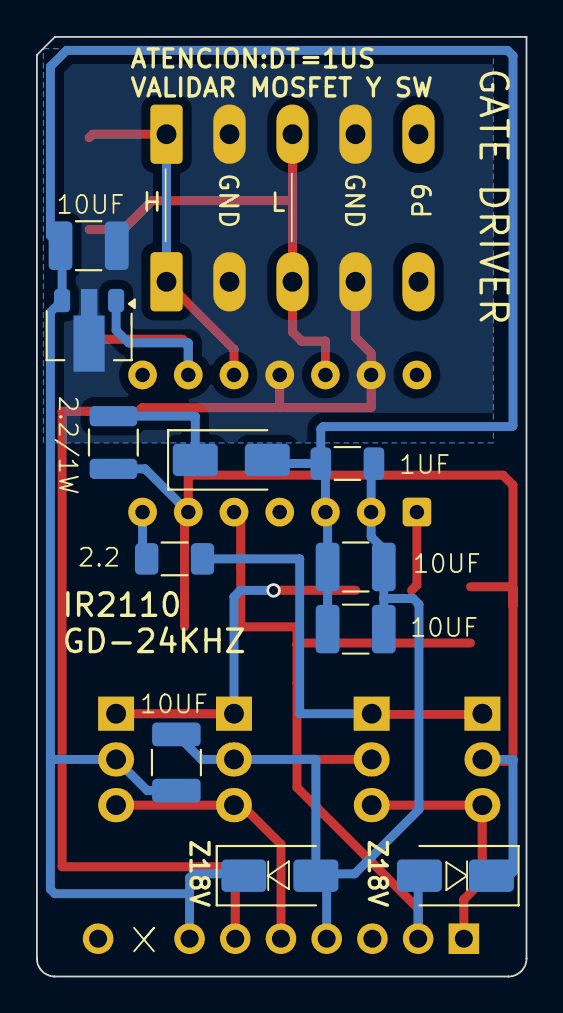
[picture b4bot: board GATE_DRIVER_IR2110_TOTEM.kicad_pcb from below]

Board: 2 copper layers, 27.2 x 52.2 mm, 25 parts (11 on the bottom side), 15 nets.
